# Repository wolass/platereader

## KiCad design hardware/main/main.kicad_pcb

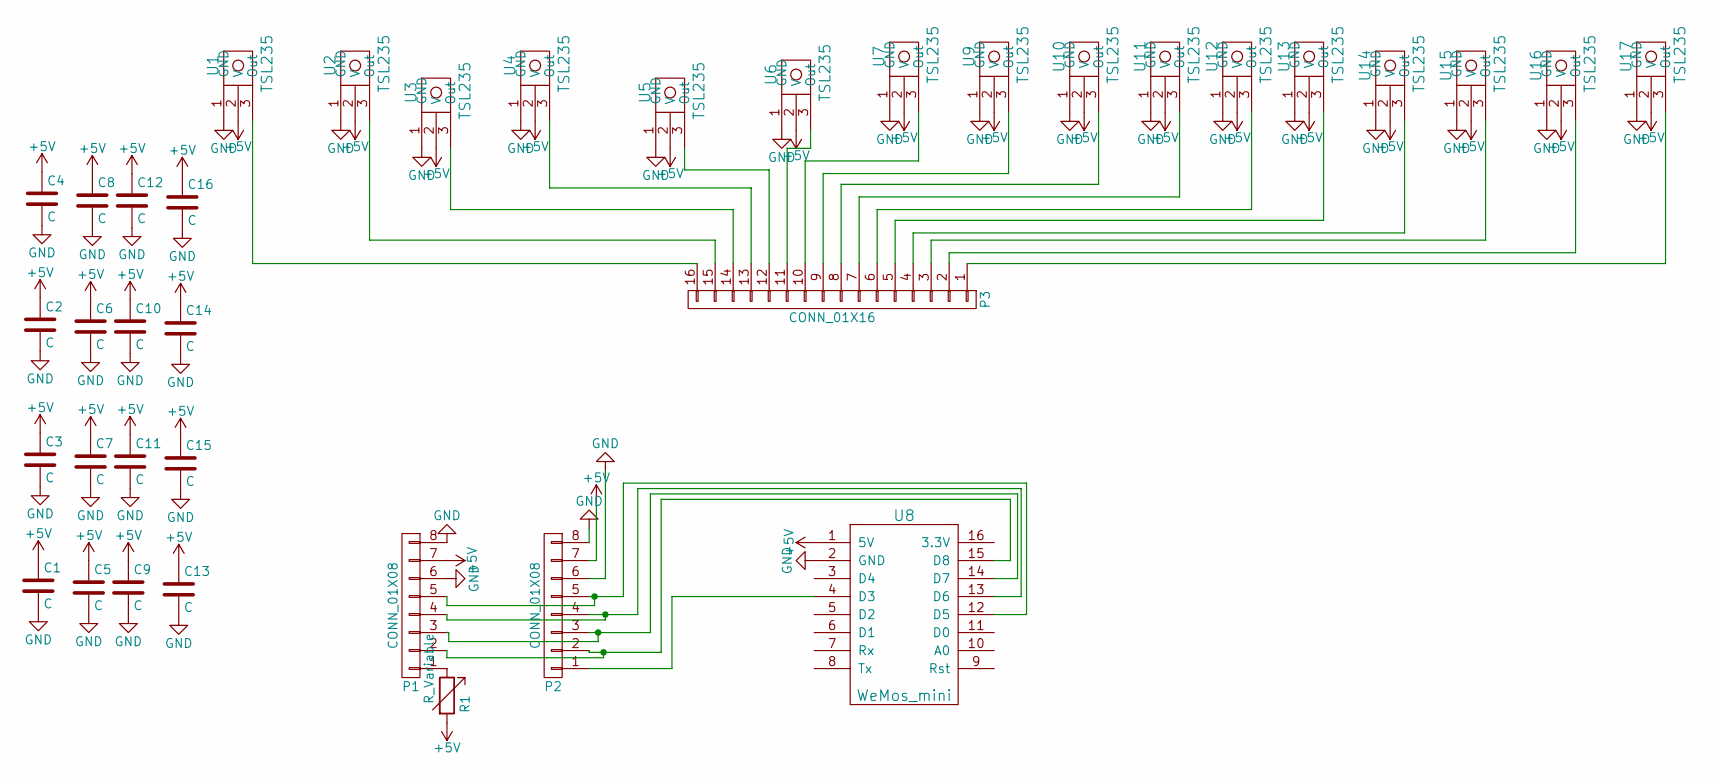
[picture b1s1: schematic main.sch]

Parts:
C1, C2, C3, C4, C5, C6, C7, C8, C9, C10, C11, C12, C13, C14, C15, C16: C; C_0805_HandSoldering
P1, P2: CONN_01X08; Socket_Strip_Straight_1x08
P3: CONN_01X16; Socket_Strip_Straight_1x16
R1: R_Variable; Potentiometer_Triwood_RM-065
U1, U2, U3, U4, U5, U6, U7, U9, U10, U11, U12, U13, U14, U15, U16, U17: TSL235
U8: WeMos_mini; D1_mini_board

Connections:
+5V: C1.1, C2.1, C3.1, C4.1, C5.1, C6.1, C7.1, C8.1, C9.1, C10.1, C11.1, C12.1, C13.1, C14.1, C15.1, C16.1, P1.7, P2.7, R1.2, U1.2 (V), U2.2 (V), U3.2 (V), U4.2 (V), U5.2 (V), U6.2 (V), U7.2 (V), U8.1 (5V), U9.2 (V), U10.2 (V), U11.2 (V), U12.2 (V), U13.2 (V), U14.2 (V), U15.2 (V), U16.2 (V), U17.2 (V)
GND: C1.2, C2.2, C3.2, C4.2, C5.2, C6.2, C7.2, C8.2, C9.2, C10.2, C11.2, C12.2, C13.2, C14.2, C15.2, C16.2, P1.6, P1.8, P2.6, P2.8, U1.1 (GND), U2.1 (GND), U3.1 (GND), U4.1 (GND), U5.1 (GND), U6.1 (GND), U7.1 (GND), U8.2 (GND), U9.1 (GND), U10.1 (GND), U11.1 (GND), U12.1 (GND), U13.1 (GND), U14.1 (GND), U15.1 (GND), U16.1 (GND), U17.1 (GND)
unnamed: P1.1, R1.1
unnamed: P1.2, P2.2, U8.15 (D8)
unnamed: P1.3, P2.3, U8.14 (D7)
unnamed: P1.4, P2.4, U8.13 (D6)
unnamed: P1.5, P2.5, U8.12 (D5)
unnamed: P2.1, U8.4 (D3)
unnamed: P3.1, U17.3 (Out)
unnamed: P3.2, U16.3 (Out)
unnamed: P3.3, U15.3 (Out)
unnamed: P3.4, U14.3 (Out)
unnamed: P3.5, U13.3 (Out)
unnamed: P3.6, U12.3 (Out)
unnamed: P3.7, U11.3 (Out)
unnamed: P3.8, U10.3 (Out)
unnamed: P3.9, U9.3 (Out)
unnamed: P3.10, U7.3 (Out)
unnamed: P3.11, U6.3 (Out)
unnamed: P3.12, U5.3 (Out)
unnamed: P3.13, U4.3 (Out)
unnamed: P3.14, U3.3 (Out)
unnamed: P3.15, U2.3 (Out)
unnamed: P3.16, U1.3 (Out)

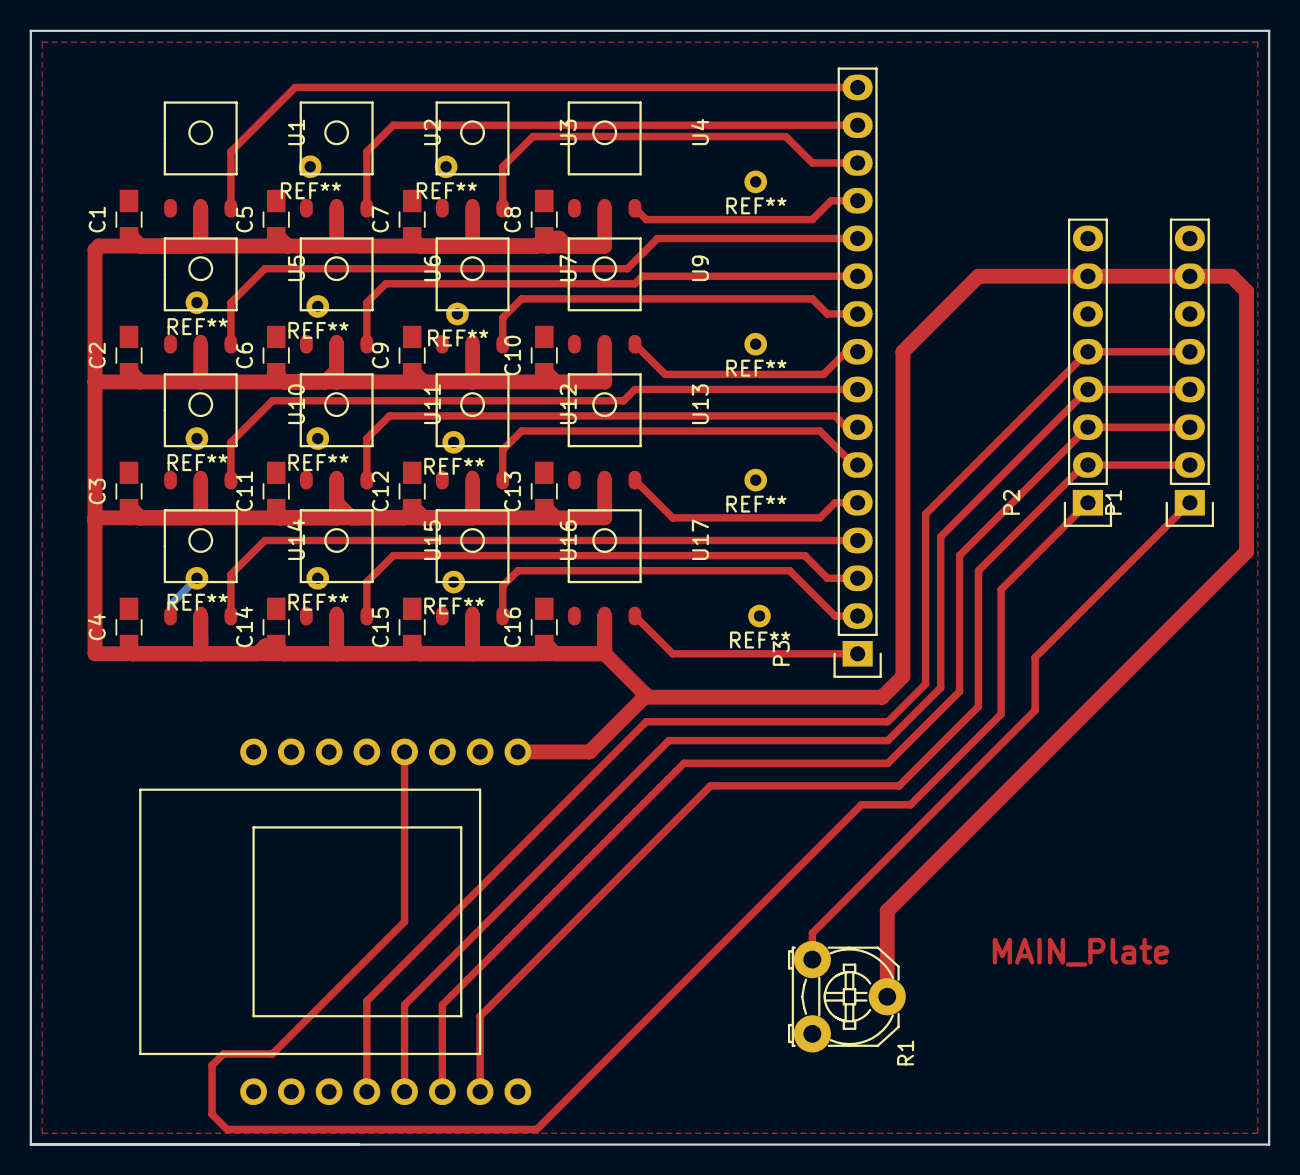
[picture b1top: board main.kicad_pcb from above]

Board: 2 copper layers, 83.3 x 74.9 mm, 37 parts (1 on the bottom side), 24 nets.

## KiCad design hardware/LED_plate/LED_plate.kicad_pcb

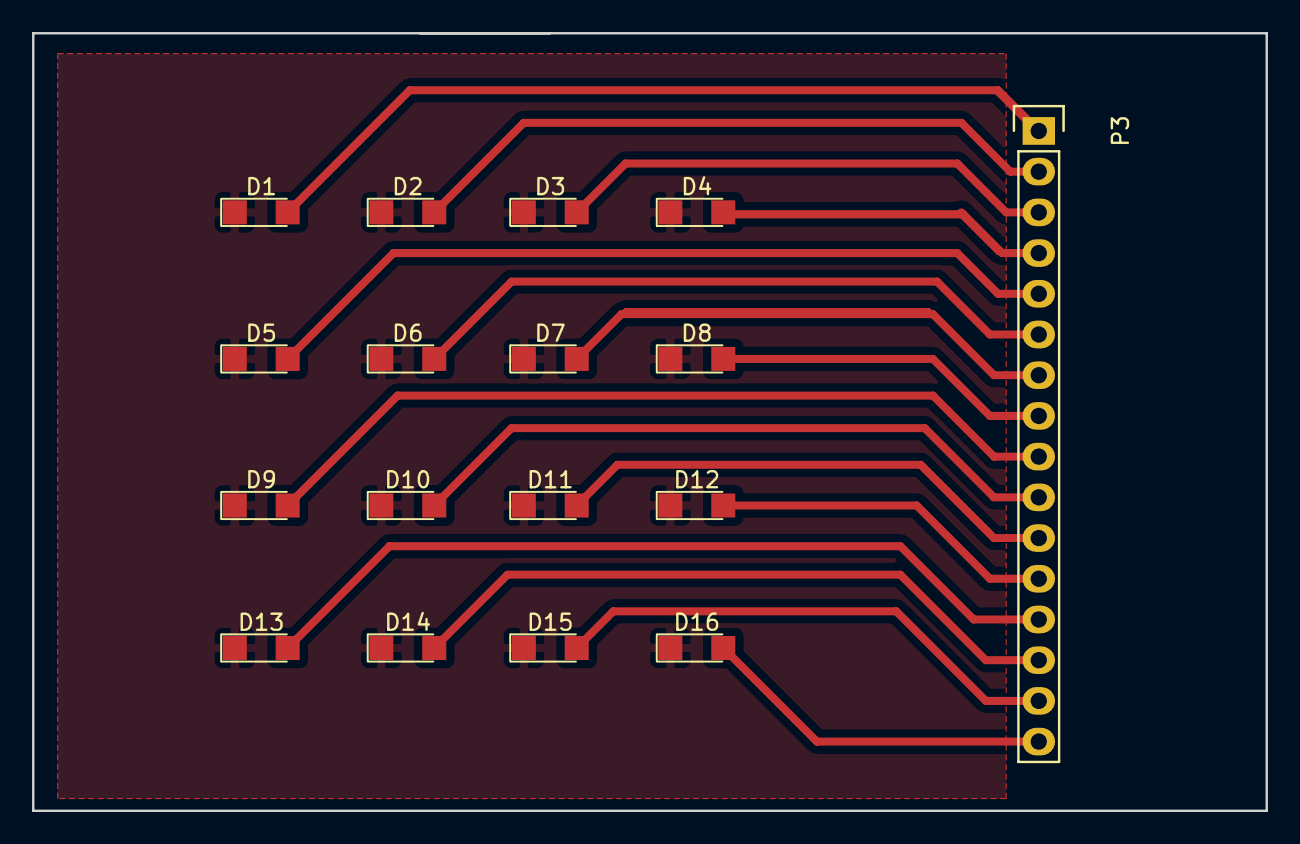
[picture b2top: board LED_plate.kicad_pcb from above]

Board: 2 copper layers, 77.0 x 48.5 mm, 17 parts (0 on the bottom side), 17 nets.

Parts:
D1, D2, D3, D4, D5, D6, D7, D8, D9, D10, D11, D12, D13, D14, D15, D16: LED; LED_1206
P3: CONN_01X16; Socket_Strip_Straight_1x16

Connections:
GND: D1.1, D2.1, D3.1, D4.1, D5.1, D6.1, D7.1, D8.1, D9.1, D10.1, D11.1, D12.1, D13.1, D14.1, D15.1, D16.1
unnamed: D1.2, P3.1
unnamed: D2.2, P3.2
unnamed: D3.2, P3.3
unnamed: D4.2, P3.4
unnamed: D5.2, P3.5
unnamed: D6.2, P3.6
unnamed: D7.2, P3.7
unnamed: D8.2, P3.8
unnamed: D9.2, P3.9
unnamed: D10.2, P3.10
unnamed: D11.2, P3.11
unnamed: D12.2, P3.12
unnamed: D13.2, P3.13
unnamed: D14.2, P3.14
unnamed: D15.2, P3.15
unnamed: D16.2, P3.16

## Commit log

2016-09-07 Megring with the turbigraph
2017-01-27 First verion of the PCBs
2017-01-27 Hotfix power line fill
2017-09-01 added text to Front layer
